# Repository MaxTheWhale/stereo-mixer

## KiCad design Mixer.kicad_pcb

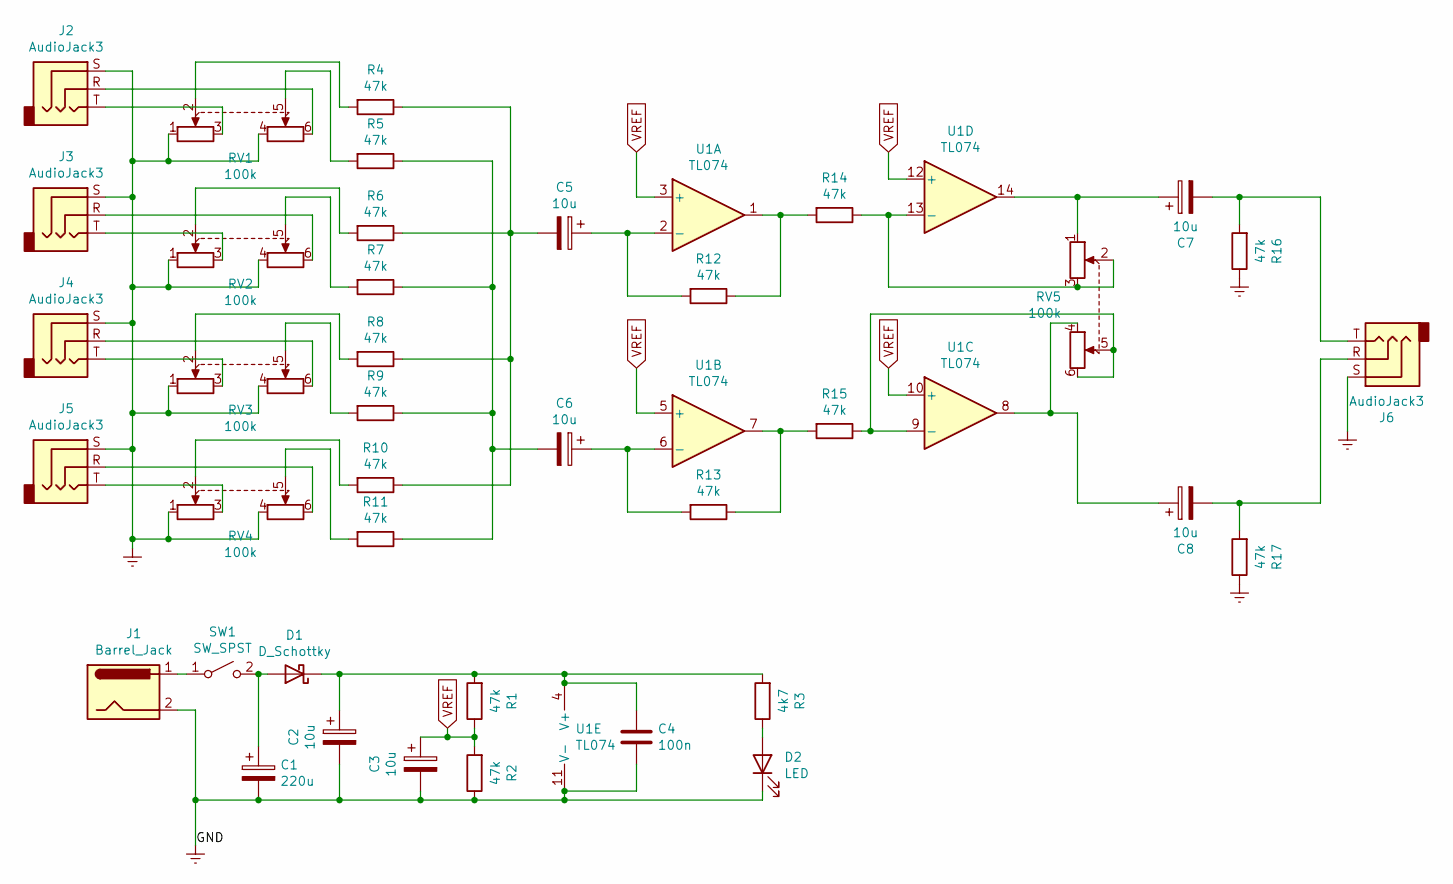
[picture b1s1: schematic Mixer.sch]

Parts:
C1: 220u; CP_Radial_D6.3mm_P2.50mm
C2, C3, C5, C6, C7, C8: 10u; CP_Radial_Tantal_D4.5mm_P5.00mm
C4: 100n; C_Disc_D7.0mm_W2.5mm_P5.00mm
D1: D_Schottky; D_A-405_P10.16mm_Horizontal
D2: LED; LED_D3.0mm
J1: Barrel_Jack; BarrelJack_Horizontal
J2, J3, J4, J5, J6: AudioJack3; CUI_SJ1-3525N
R1, R2, R4, R5, R6, R7, R8, R9, R10, R11, R12, R13, R14, R15, R16, R17: 47k; R_Axial_DIN0207_L6.3mm_D2.5mm_P10.16mm_Horizontal
R3: 4k7; R_Axial_DIN0207_L6.3mm_D2.5mm_P10.16mm_Horizontal
RV1, RV2, RV3, RV4, RV5: 100k; Potentiometer_Alps_RK163_Dual_Horizontal
SW1: SW_SPST; SW_CuK_OS202013MT5QN1_DPDT_Straight
U1: TL074; DIP-14_W7.62mm

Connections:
Earth: C1.2, C2.2, C3.2, C4.2, D2.1 (K), J1.2, J2.S, J3.S, J4.S, J5.S, J6.S, R2.1, R16.1, R17.1, RV1.1, RV1.4, RV2.1, RV2.4, RV3.1, RV3.4, RV4.1, RV4.4, U1.11 (V-)
unnamed: C1.1, D1.2 (A), SW1.2 (B)
unnamed: C2.1, C4.1, D1.1 (K), R1.2, R3.2, U1.4 (V+)
unnamed: C5.1, R12.2, U1.2 (-)
unnamed: C5.2, R4.1, R6.1, R8.1, R10.1
unnamed: C6.1, R13.2, U1.6 (-)
unnamed: C6.2, R5.1, R7.1, R9.1, R11.1
unnamed: C7.1, RV5.1, U1.14
unnamed: C7.2, J6.T, R16.2
unnamed: C8.1, RV5.4, U1.8
unnamed: C8.2, J6.R, R17.2
unnamed: D2.2 (A), R3.1
unnamed: J1.1, SW1.1 (A)
unnamed: J2.R, RV1.6
unnamed: J2.T, RV1.3
unnamed: J3.R, RV2.6
unnamed: J3.T, RV2.3
unnamed: J4.R, RV3.6
unnamed: J4.T, RV3.3
unnamed: J5.R, RV4.6
unnamed: J5.T, RV4.3
unnamed: R4.2, RV1.2
unnamed: R5.2, RV1.5
unnamed: R6.2, RV2.2
unnamed: R7.2, RV2.5
unnamed: R8.2, RV3.2
unnamed: R9.2, RV3.5
unnamed: R10.2, RV4.2
unnamed: R11.2, RV4.5
unnamed: R12.1, R14.2, U1.1
unnamed: R13.1, R15.2, U1.7
unnamed: R14.1, RV5.2, RV5.3, U1.13 (-)
unnamed: R15.1, RV5.5, RV5.6, U1.9 (-)
VREF: C3.1, R1.1, R2.2, U1.3 (+), U1.5 (+), U1.10 (+), U1.12 (+)

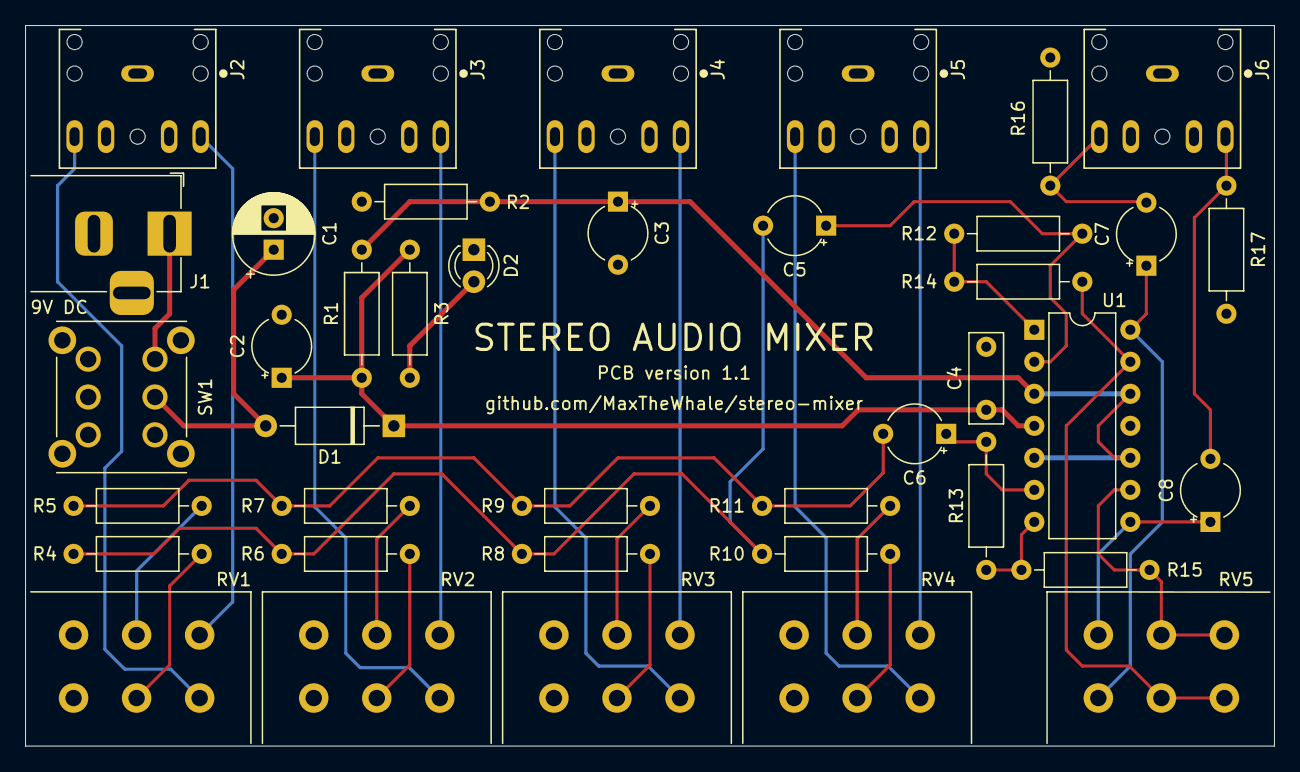
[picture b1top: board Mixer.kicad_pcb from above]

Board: 2 copper layers, 99.1 x 57.2 mm, 40 parts (0 on the bottom side), 34 nets.

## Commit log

2020-09-20 Add gitignore and update PCB
2020-09-20 Add libraries
